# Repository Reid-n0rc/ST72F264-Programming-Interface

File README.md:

# ST72F264 Programming Interface
 Programming Interface for ST72F264

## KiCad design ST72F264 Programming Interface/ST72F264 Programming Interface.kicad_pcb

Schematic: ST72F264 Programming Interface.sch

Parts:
J1: Conn_02x05_Odd_Even; PinHeader_2x5_P2.54mm_Drill1.02mm
JP1: SolderJumper_2_Bridged; SMT-JUMPER_2_NC_TRACE_NO-SILK
R1: 10K; R_0805_2012Metric_Pad1.15x1.40mm_HandSolder
TP1, TP2: TestPoint; TestPoint_Keystone_5019_Minature
U1: ST72F264; DIP-32_400_ELL
Y1: Resonator; CERALOK_TH; MPN CSTLS16M0X53Z-A0

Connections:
GND: J1.1, J1.3, J1.5, J1.10, R1.2, TP2.1, U1.31, Y1.2
ICCCLK: J1.4, U1.29
ICCDATA: J1.2, U1.28
ICCSEL: J1.8, R1.1, U1.30
unnamed: JP1.2 (B), U1.2, Y1.1
unnamed: U1.3, Y1.3
OSC: J1.9, JP1.1 (A)
VDD: J1.7, TP1.1, U1.32
~RESET: J1.6, U1.1

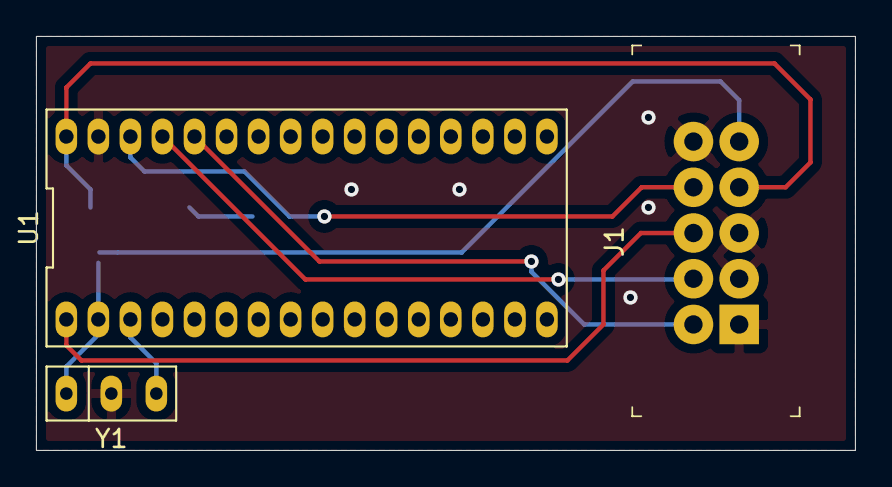
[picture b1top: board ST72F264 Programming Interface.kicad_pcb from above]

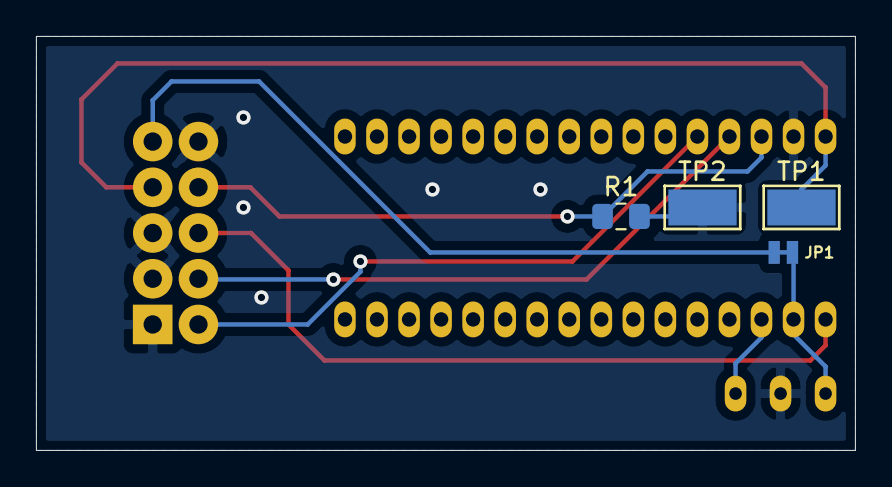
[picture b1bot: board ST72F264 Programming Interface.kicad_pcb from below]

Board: 2 copper layers, 45.5 x 23.0 mm, 7 parts (4 on the bottom side), 9 nets.

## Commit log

2020-11-18 Board layout for production
    Rev A of PCB layout
